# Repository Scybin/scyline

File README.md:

# chitin

## 📚 Table of Contents

- [⚠️ Disclaimer](#disclaimer)
- [⌨️ Welcome](#welcome)
- [⚙️ Features](#features)
- [📊 Project Status](#project-status)
- [📦 Parts List](#parts-list)
- [🛠️ Build Guide](#build-guide)
- [💾 Firmware](#firmware)
- [📄 License](#license)

## ⚠️ Disclaimer

This project has reached the fully working prototype stage. All core features have been tested and function as intended. However, as with any DIY hardware project, you should carefully review all files before manufacturing or assembly. The author(s) cannot guarantee flawless operation in every environment or configuration.

The author(s) take no responsibility for any damage, issues, or legal trouble that might result from using this project (see the license). Be sure to follow local laws regarding radio frequencies and DIY electronics.

## ⌨️ Welcome

Chitin is a custom, open-source mechanical keyboard designed for ergonomic comfort, wireless functionality, and trackball. The design is built off my original keyboard design: scyboard, a minimal keyboard design.

## ⚙️ Features

- Ergonomic ortholinear layout
- ZMK firmware support
- USB-C connectivity & battery charging
- Bluetooth compatible
- Customizable keymaps, layers, and macros
- Trackball which can be programmed as a pointing device
- Layout is declared using Ergogen
- KiCad traces auto-routed using Freerouting
- Open source

## 📊 Project Status

The prototype design is complete. Waiting for hardware to build keyboard.

## 📦 Parts List

*I am not sponsored or affiliated with the vendors linked below. This is where I prefer to purchase my products.*

| Part                      | Quantity | Description                                     | Purchase Link                                                                                                          | Datasheet                                                                                                                           |
|---------------------------|----------|-------------------------------------------------|----------------------------------------------------------------------------------------------------------------------- |-------------------------------------------------------------------------------------------------------------------------------------------|
| Microcontroller           |    2     | nice!nano v2.0                                  | [Nice Keyboarrds nice!nano v2.0](https://typeractive.xyz/products/no-solder-spring-headers?variant=47196312502503)     | [Nordic nRF52840](https://nicekeyboards.com/nice-nano)                                                                                    | 
| Pin Headers               |    4     | Controller socketing system (4mm)               | [MAC8 spring-loaded pin headers](https://www.littlekeyboards.com/products/spring-header-12-pin?variant=40197938675779) | [MAC8 spring-loaded pin headers specifications](https://www.mac8sdk.co.jp/uploads/entry_meta/file_value/1117/mac8_2018a_jp-xb2.pdf)       |
| Reset Button              |    2     | Panasonic miniature momentary button            | [Panasonic Reset Button](https://typeractive.xyz/products/reset-button)                                                | [EVQPUC02K](https://cdn.shopify.com/s/files/1/0618/5674/3655/files/PANASONIC-EVQPUC02K.pdf)                                               |
| Power Switch              |    2     | Alps miniature SPDT switch                      | [ALPS Powr Switch](https://typeractive.xyz/products/power-switch)                                                      | [SSSS811101](https://cdn.shopify.com/s/files/1/0618/5674/3655/files/ALPS-SSSS811101.pdf)                                                  |
| Battery Connector         |    2     | JST PH 2.0mm                                    | [JST Battery Jack](https://typeractive.xyz/products/battery-jack)                                                      | [JST_PH_S2B-PH-K_1x02_P2.00mm_Horizontal](http://www.jst-mfg.com/product/pdf/eng/ePH.pdf)                                                 |
| Battery                   |    2     | 3.7V LiPo 1200mAh (w/ JST adapter)              | [Lithium Ion Polymer Battery - 3.7v 1200mAh](https://www.adafruit.com/product/258)                                     | [301230](https://cdn-shop.adafruit.com/product-files/258/C101-_Li-Polymer_503562_1200mAh_3.7V_with_PCM_APPROVED_8.18.pdf)                 |
| Diode                     |    57    | SMD Diode                                       | [Semtech SMD Diodes](https://typeractive.xyz/products/smd-diodes)                                                      | [SOD-123](https://www.onsemi.com/download/data-sheet/pdf/mmsd301t1-d.pdf)      									                          |
| Hotswap Socket            |    57    | Kailh MX PCB Socket                             | [Kailh Hotswap Sockets](https://typeractive.xyz/products/hotswap-sockets)                                              | [CPG151101S11](https://www.kailhswitch.com/Content/upload/pdf/202215927/CPG151101S11-16.pdf?rnd=181)                                      |
| MX Switch                 |    57    | JWICK Linear Switches                           | [JWK JWICK Linear Switches](https://typeractive.xyz/products/jwk-jwick-linear-switches)                                | [MX Series Keyswitch](https://cdn.sparkfun.com/datasheets/Components/Switches/MX%20Series.pdf)                                            |
| MX Keycap                 |    57    | 55 x 1u, 2 x 1.5u                               | [DSA Keycaps](https://typeractive.xyz/products/dsa-keycaps)                                                            | [DSA Keycap Project](https://drive.google.com/drive/folders/0B0LNjZf_tzjWZGhwZ0VKUm9PQVE?resourcekey=0-rYUAMYD1-22Btlgdmpb0IQ)            |
| M2x15 Standoff            |    18    | Standoffs for plate                             | [Newark M2x15 Standoff](https://www.newark.com/wurth-elektronik/970150244/standoff-brass-hex-f-f-m2-15mm/dp/46AJ4338)  | [Farnell Datasheet](https://www.farnell.com/cad/3209262.pdf)                                                                              |
| M2x5e Screw                |    8     | Screws to connect bottom case to top case       | [CO-RODE Screw Kit](https://www.amazon.com/gp/product/B01FTI8TM8/)                                                     |                                                                                                                                           |
| M2x6 Screw                |    18    | Screws for bottom case and top plate            | [CO-RODE Screw Kit](https://www.amazon.com/gp/product/B01FTI8TM8/)                                                     |                                                                                                                                           |
| M2.5x8 Screw              |    4     | Screws to hold trackball in top case            | [CO-RODE Screw Kit](https://www.amazon.com/gp/product/B01FTI8TM8/)                                                     |                                                                                                                                           |
| M2x3 Insert Nut           |    8     | Inserts for top cases                           | [uxcell Knurled Insert Nuts](https://www.amazon.com/dp/B07LBQFNQD?th=1)                                                |                                                                                                                                           |
| M2.5x2 Nut                |    4     | Nuts to hold trackball in top case              | [Newark M2.5 Hex Nuts](https://www.newark.com/tr-fastenings/m2-5-hfst-z100/full-nut-steel-bzp-m2-5/dp/53M8595)         | [Farnell Datasheet](https://www.farnell.com/datasheets/2644739.pdf)                                                                       |
| Trackball Breakout        |    1     | Pimoroni RGBW Trackball Breakout                | [Trackball Breakout by Pimoroni](https://shop.pimoroni.com/products/trackball-breakout?variant=27672765038675)         | [Trackball Dimensions](https://cdn.shopify.com/s/files/1/0174/1800/files/trackballbreakout.png?v=1599645804)                              |
| Qwiic Connector           |    1     | JST SH 4-pin Right Angle Connector              | [JST SH 4-pin Right Angle Connector (10-pack) - Qwiic Compatible](https://www.adafruit.com/product/4208)               | [KAWEEI TECHNOLOGY 1.0MM WAFER 90 SMT TYPE REEL PACKAGE](https://cdn-shop.adafruit.com/product-files/4208/4208_Kaweei_C13396_diagram.pdf) |
| Bottom Case               |    2     | 3D printed bottom case                          | [Case Files Found Here](https://github.com/Scybin/chitin/tree/master/3d)                                               |                                                                                                                                           |
| Top Case                  |    2     | 3D printed top case (tb case for trackball)     | [Case Files Found Here](https://github.com/Scybin/chitin/tree/master/3d)                                               |                                                                                                                                           | 

**NOTE: The trackball replaces the position of 1 switch from the keyboard layout. If not incorporating a trackball in the build, add 1 quantity to each of the following parts:**
- Diode
- Hotswap Socket
- MX Switch
- 1u MX Keycap

## 🛠️ Build Guide

TODO

## 💾 Firmware

To get started, I recommend forking my personal repository for chitin here: [zmk-config-chitin](https://github.com/Scybin/zmk-config-chitin). Making modifications to the keyboard can be done within the config folder. To flash the keyboard, follow the flashing instructions in the [ZMK docs](https://zmk.dev/docs).

My build sets the central device to the right half of the keyboard, and the peripheral to the left half. Making changes to which half the trackball resides on, or excluding the trackball from the build requires many changes to the code in the chitin repository and source module.

The repository uses my chitin ZMK module here: [zmk-keyboard-chitin](https://github.com/Scybin/zmk-keyboard-chitin), and my Pimoroni trackball driver module (derived from mwandzik's driver) here: [zmk-driver-pim447](https://github.com/Scybin/zmk-driver-pim447).

## 📄 License

This project is licensed under the MIT License. See the [LICENSE](LICENSE) file for details.

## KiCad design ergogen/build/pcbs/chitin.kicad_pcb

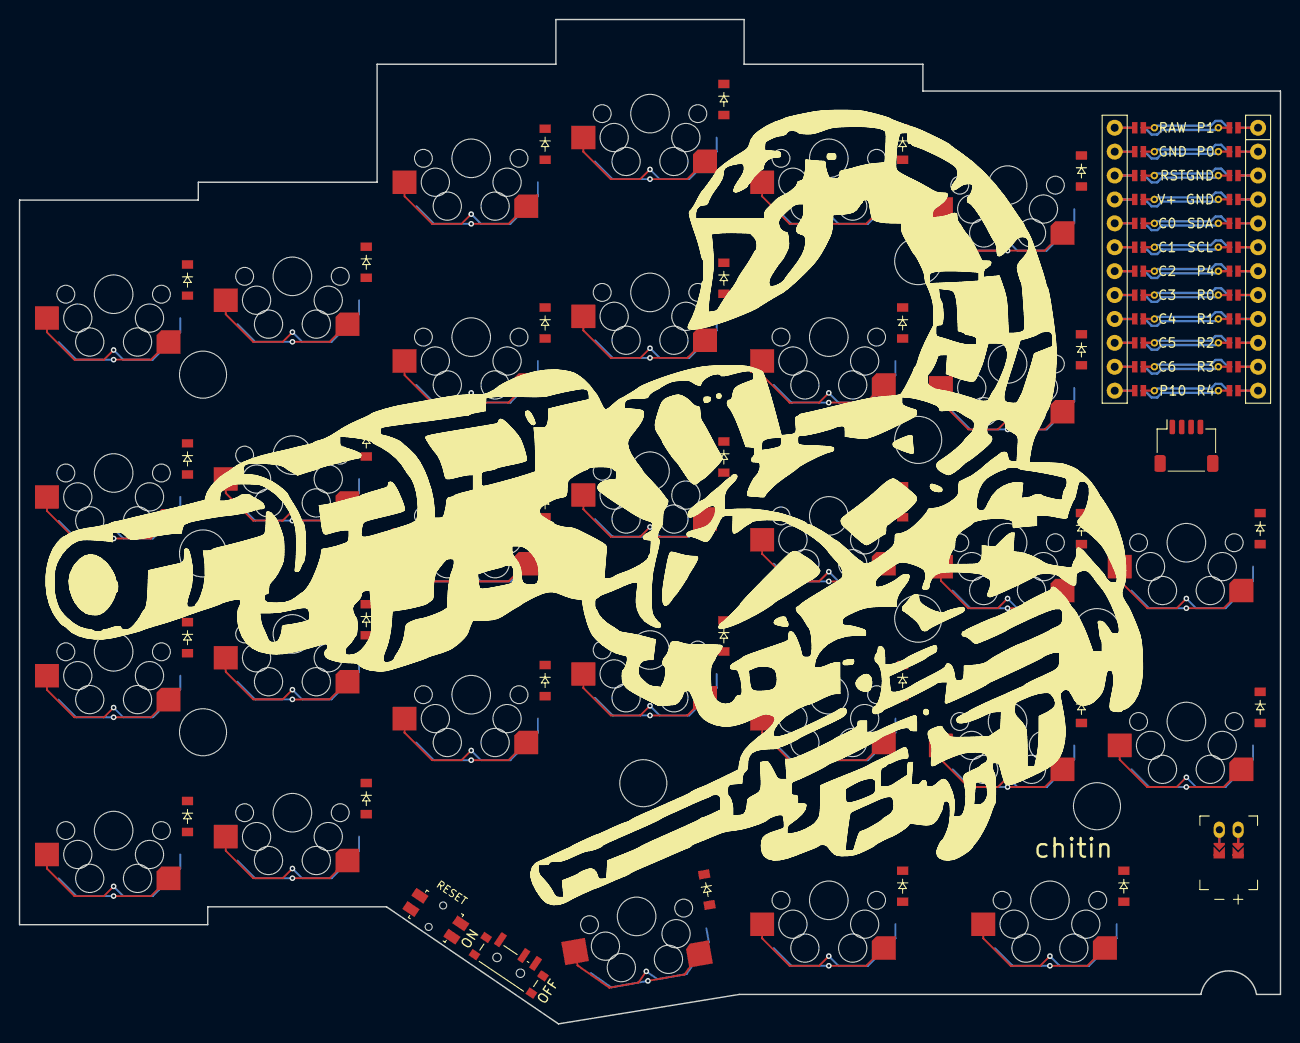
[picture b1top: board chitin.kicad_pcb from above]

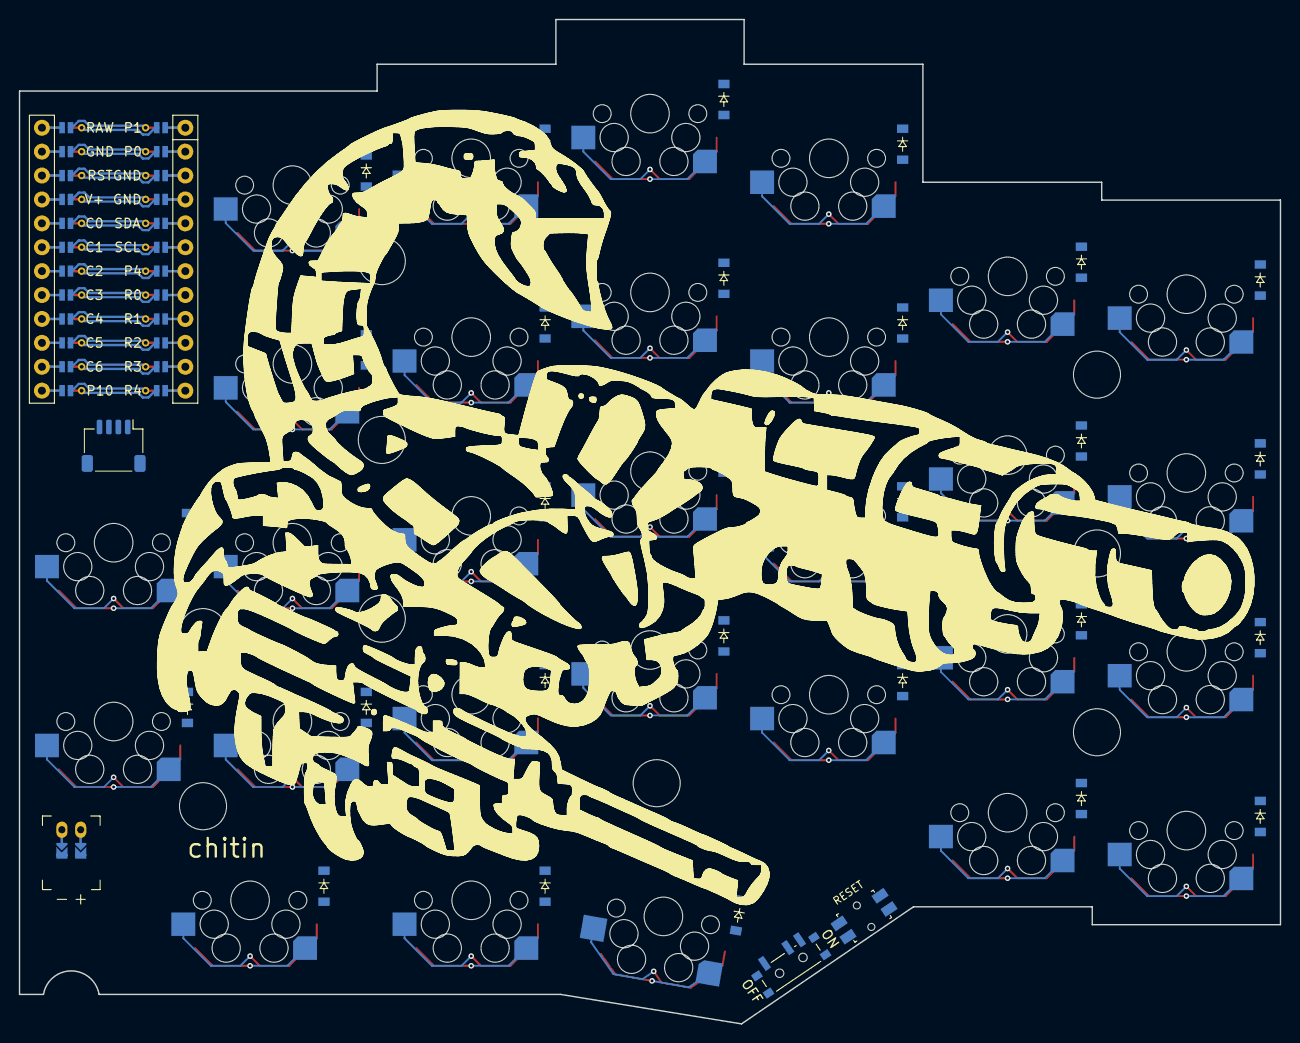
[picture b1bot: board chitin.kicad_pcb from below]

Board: 2 copper layers, 134.0 x 106.7 mm, 102 parts (58 on the bottom side), 50 nets.

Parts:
D1, D2, D3, D4, D5, D6, D7, D8, D9, D10, D11, D12, D13, D14, D15, D16, D17, D18, D19, D20, D21, D22, D23, D24, D25, D26, D27, D28, D29, D30, D31, D32, D33, D34, D35, D36, D37, D38, D39, D40, D41, D42, D43, D44, D45, D46, D47, D48, D49, D50, D51, D52, D53, D54, D55, D56, D57, D58: diode_tht_sod123
J1: qwiik_jst
JST1: battery_connector_jst_ph_2
LOGO1: logo_dual_chitin
MCU1: mcu_nice_nano
MH1, MH2, MH3, MH4, MH5, MH6, MH7, MH8, MH9: mounting_hole_npth
PWR1: power_switch_smd_side
RST1: reset_switch_smd_side
S1, S2, S3, S4, S5, S6, S7, S8, S9, S10, S11, S12, S13, S14, S15, S16, S17, S18, S19, S20, S21, S22, S23, S24, S25, S26, S27, S28, S29: switch_mx

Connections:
BAT_P: JST1.1, PWR1.1, PWR1.3
C0: MCU1.120, S1.1, S2.1, S3.1, S4.1
C1: MCU1.119, S5.1, S6.1, S7.1, S8.1
C2: MCU1.118, S9.1, S10.1, S11.1, S12.1, S25.1
C3: MCU1.117, S13.1, S14.1, S15.1, S16.1, S26.1
C4: MCU1.116, S17.1, S18.1, S19.1, S20.1, S27.1
C5: MCU1.115, S21.1, S22.1, S23.1, S24.1
C6: MCU1.114, S28.1, S29.1
GND: J1.1, JST1.2, MCU1.103, MCU1.104, MCU1.123, RST1.1, RST1.3
JST1_1: JST1.11, JST1.21, JST1.31
JST1_2: JST1.12, JST1.22, JST1.32
R0: D4.1, D8.1, D12.1, D16.1, D20.1, D24.1, D33.1, D37.1, D41.1, D45.1, D49.1, D53.1, MCU1.108
R1: D3.1, D7.1, D11.1, D15.1, D19.1, D23.1, D32.1, D36.1, D40.1, D44.1, D48.1, D52.1, MCU1.109
R2: D2.1, D6.1, D10.1, D14.1, D18.1, D22.1, D29.1, D31.1, D35.1, D39.1, D43.1, D47.1, D51.1, D58.1, MCU1.110
R3: D1.1, D5.1, D9.1, D13.1, D17.1, D21.1, D28.1, D30.1, D34.1, D38.1, D42.1, D46.1, D50.1, D57.1, MCU1.111
R4: D25.1, D26.1, D27.1, D54.1, D55.1, D56.1, MCU1.112
RAW: MCU1.124, PWR1.2
RST: MCU1.122, RST1.2, RST1.4
SCL: J1.4, MCU1.106
SDA: J1.3, MCU1.105
V+: J1.2, MCU1.121
index_bottom_B: D17.2, D46.2, S17.2
index_home_B: D18.2, D47.2, S18.2
index_top_B: D20.2, D49.2, S20.2
index_upper_B: D19.2, D48.2, S19.2
inner_bottom_B: D21.2, D50.2, S21.2
inner_home_B: D22.2, D51.2, S22.2
inner_top_B: D24.2, D53.2, S24.2
inner_upper_B: D23.2, D52.2, S23.2
layer_cluster_B: D26.2, D55.2, S26.2
macro_bottom_B: D28.2, D57.2, S28.2
macro_home_B: D29.2, D58.2, S29.2
middle_bottom_B: D13.2, D42.2, S13.2
middle_home_B: D14.2, D43.2, S14.2
middle_top_B: D16.2, D45.2, S16.2
middle_upper_B: D15.2, D44.2, S15.2
outer_bottom_B: D1.2, D30.2, S1.2
outer_home_B: D2.2, D31.2, S2.2
outer_top_B: D4.2, D33.2, S4.2
outer_upper_B: D3.2, D32.2, S3.2
pinky_bottom_B: D5.2, D34.2, S5.2
pinky_home_B: D6.2, D35.2, S6.2
pinky_top_B: D8.2, D37.2, S8.2
pinky_upper_B: D7.2, D36.2, S7.2
ring_bottom_B: D9.2, D38.2, S9.2
ring_home_B: D10.2, D39.2, S10.2
ring_top_B: D12.2, D41.2, S12.2
ring_upper_B: D11.2, D40.2, S11.2
space_cluster_B: D27.2, D56.2, S27.2
tuck_cluster_B: D25.2, D54.2, S25.2

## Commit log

2025-12-14 Push initial config
2025-12-15 Update config
2025-12-15 Push updates
2025-12-15 Push changes
2025-12-18 Add ceoloide footprints
2025-12-18 Update ignore list
2025-12-18 Generate Ergogen output
2025-12-18 Add exclusion
2025-12-18 Add 3d models
2025-12-18 Add kicad 3d models
2025-12-19 Build
2025-12-19 Update column and row references
2025-12-19 Comment out qwiic_jst configuration
    Comment out qwiic_jst configuration section in config.yaml
2025-12-19 Refactor JST variables and adjust extrude values
    Updated variable names for JST connectors and adjusted extrude values for switchplate and walls.
2025-12-19 Update extrude values for outer and inner walls
2025-12-20 Remove extra files
2025-12-20 Compile
2025-12-24 Refactor config variables and add insert points
    Updated variable names for clarity and added new insert points.
2025-12-24 Comment out unused pins in config.yaml
2025-12-24 Add notch for JST PH wires in config.yaml
    Added notch for JST PH wires in config.
2025-12-24 Add PCB notch configuration to config.yaml
2025-12-24 Modify plate_hole and full_case definitions
    Updated plate_hole configuration and modified full_case structure.
2025-12-24 Define bottom lip wall and cut in config.yaml
    Added bottom lip wall and cut definitions to the config.
2025-12-27 Add ergogen-footprints submodule
2025-12-27 Add scybin-footprints submodule
2025-12-27 Update exclusions
2025-12-27 Add scybin footprints
2025-12-27 Track scybin footprints as regular files
2025-12-27 Update license
2025-12-27 Rename keyboard
2025-12-27 Rename kicad 3d library
2025-12-27 Add additional exclusion
2025-12-28 Add exclusions
2025-12-28 Finalize PCB with Freerouting
2025-12-28 Generate gerbers
2025-12-28 Clean up formatting
2025-12-28 Add 3d print models
2025-12-28 Rename wall_cover_case to top_case
2025-12-28 Rename case files
2025-12-31 Update parts
2026-01-09 Update case holes
2026-01-09 Update case files for increased hole sizes
2026-01-09 Add parts
2026-01-19 Revise README
2026-01-20 Update parts list
